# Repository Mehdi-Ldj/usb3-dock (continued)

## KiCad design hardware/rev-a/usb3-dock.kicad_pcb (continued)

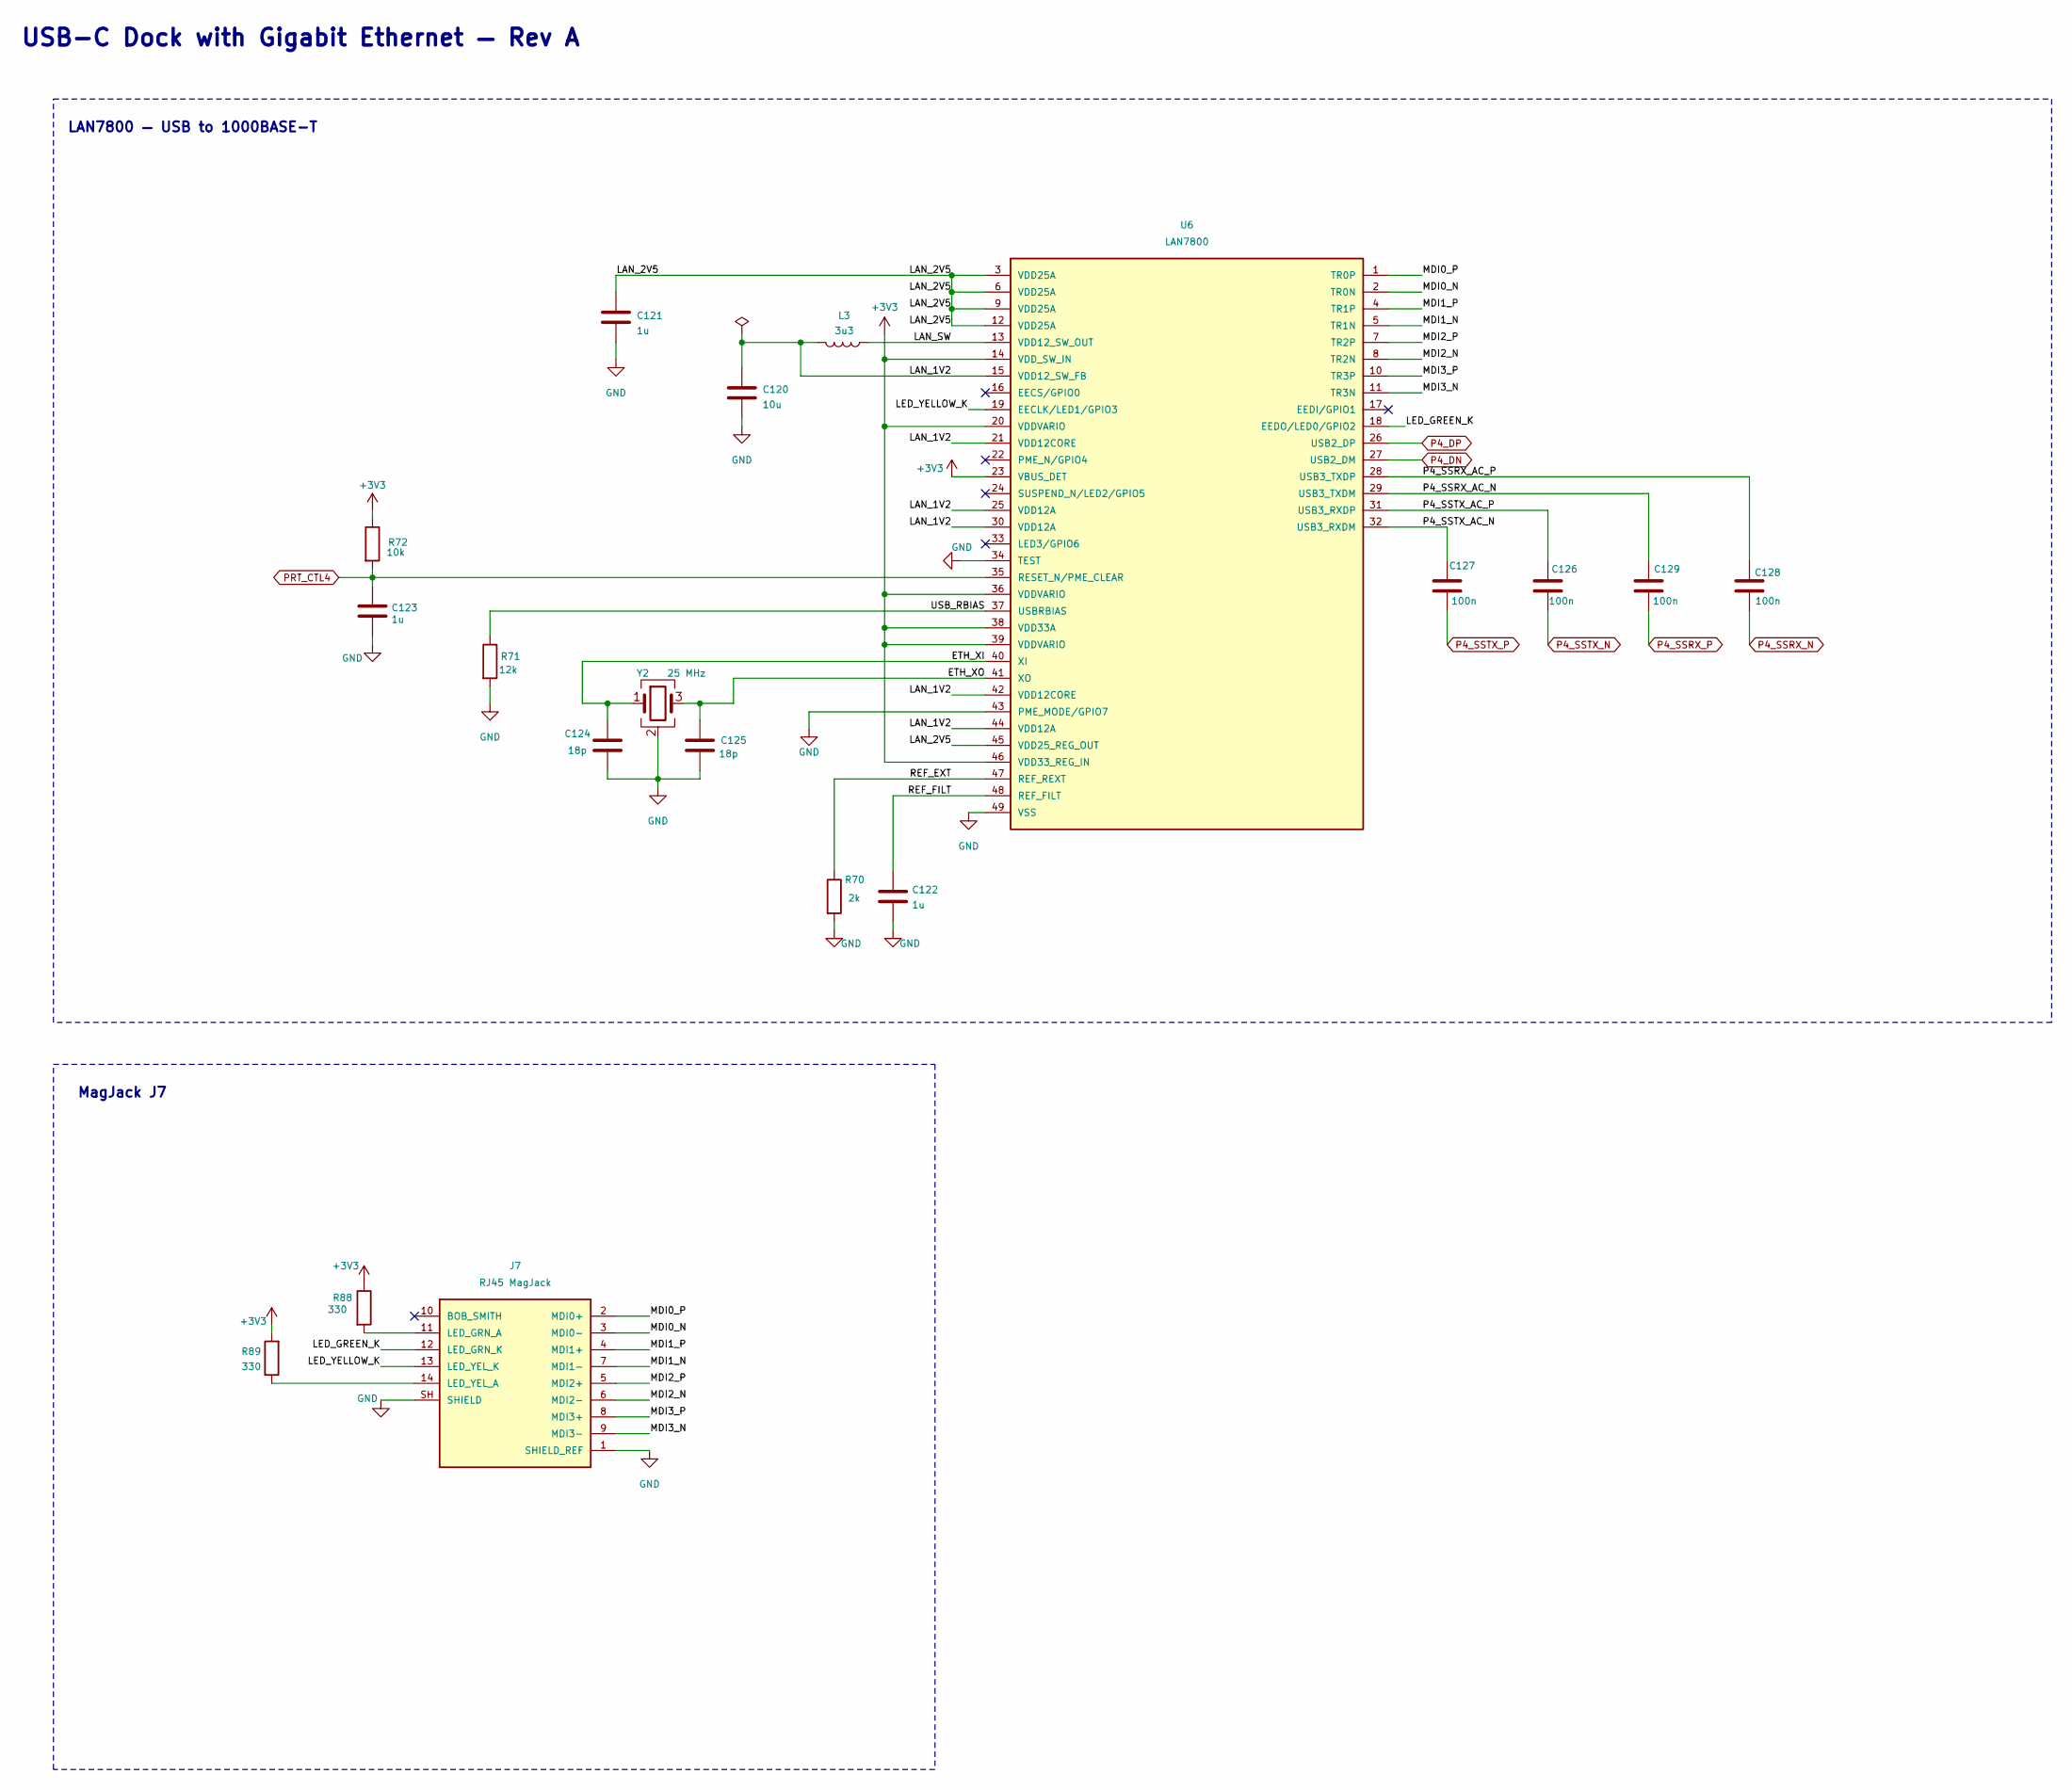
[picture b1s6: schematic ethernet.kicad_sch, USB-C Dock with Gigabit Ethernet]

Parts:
C120: 10u; C_0805_2012Metric
C121, C122, C123: 1u; C_0603_1608Metric
C124, C125: 18p; C_0402_1005Metric
C126, C127, C128, C129: 100n; C_0402_1005Metric
J7: RJ45 MagJack; RJ45_Hanrun_HR911130A
L3: 3u3; L_4x4mm_FNR4030
R70: 2k; R_0603_1608Metric
R71: 12k; R_0603_1608Metric
R72: 10k; R_0603_1608Metric
R88, R89: 330; R_0603_1608Metric
U6: LAN7800; QFN-48-1EP_6x6mm_P0.4mm_EP4.3x4.3mm
Y2: 25 MHz; Crystal_SMD_3225-4Pin_3.2x2.5mm

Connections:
+3V3: R72.1, R88.1, R89.2, U6.14 (VDD_SW_IN), U6.20 (VDDVARIO), U6.23 (VBUS_DET), U6.36 (VDDVARIO), U6.38 (VDD33A), U6.39 (VDDVARIO), U6.46 (VDD33_REG_IN); also elsewhere on the board
/ethernet/ETH_XI: C124.1, U6.40 (XI), Y2.1
/ethernet/ETH_XO: C125.1, U6.41 (XO), Y2.3
/ethernet/LAN_1V2: C120.1, L3.2, U6.15 (VDD12_SW_FB), U6.21 (VDD12CORE), U6.25 (VDD12A), U6.30 (VDD12A), U6.42 (VDD12CORE), U6.44 (VDD12A)
/ethernet/LAN_2V5: C121.1, U6.3 (VDD25A), U6.6 (VDD25A), U6.9 (VDD25A), U6.12 (VDD25A), U6.45 (VDD25_REG_OUT)
/ethernet/LAN_SW: L3.1, U6.13 (VDD12_SW_OUT)
/ethernet/LED_GREEN_K: J7.12 (LED_GRN_K), U6.18 (EEDO/LED0/GPIO2)
/ethernet/LED_YELLOW_K: J7.13 (LED_YEL_K), U6.19 (EECLK/LED1/GPIO3)
/ethernet/MDI0_N: J7.3 (MDI0-), U6.2 (TR0N)
/ethernet/MDI0_P: J7.2 (MDI0+), U6.1 (TR0P)
/ethernet/MDI1_N: J7.7 (MDI1-), U6.5 (TR1N)
/ethernet/MDI1_P: J7.4 (MDI1+), U6.4 (TR1P)
/ethernet/MDI2_N: J7.6 (MDI2-), U6.8 (TR2N)
/ethernet/MDI2_P: J7.5 (MDI2+), U6.7 (TR2P)
/ethernet/MDI3_N: J7.9 (MDI3-), U6.11 (TR3N)
/ethernet/MDI3_P: J7.8 (MDI3+), U6.10 (TR3P)
/ethernet/P4_SSRX_AC_N: C129.2, U6.29 (USB3_TXDM)
/ethernet/P4_SSRX_AC_P: C128.2, U6.28 (USB3_TXDP)
/ethernet/P4_SSTX_AC_N: C127.2, U6.32 (USB3_RXDM)
/ethernet/P4_SSTX_AC_P: C126.2, U6.31 (USB3_RXDP)
/ethernet/REF_EXT: R70.1, U6.47 (REF_REXT)
/ethernet/REF_FILT: C122.1, U6.48 (REF_FILT)
/ethernet/USB_RBIAS: R71.1, U6.37 (USBRBIAS)
GND: C120.2, C121.2, C122.2, C123.2, C124.2, C125.2, J7.1 (SHIELD_REF), J7.SH (SHIELD), R70.2, R71.2, U6.34 (TEST), U6.43 (PME_MODE/GPIO7), U6.49 (VSS), Y2.2 (G), Y2.4 (G); also elsewhere on the board
unnamed: J7.11 (LED_GRN_A), R88.2
unnamed: J7.14 (LED_YEL_A), R89.1
P4_DN: U6.27 (USB2_DM); also elsewhere on the board
P4_DP: U6.26 (USB2_DP); also elsewhere on the board
P4_SSRX_N: C128.1; also elsewhere on the board
P4_SSRX_P: C129.1; also elsewhere on the board
P4_SSTX_N: C126.1; also elsewhere on the board
P4_SSTX_P: C127.1; also elsewhere on the board
PRT_CTL4: C123.1, R72.2, U6.35 (RESET_N/PME_CLEAR); also elsewhere on the board

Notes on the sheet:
MagJack J7
USB-C Dock with Gigabit Ethernet — Rev A
LAN7800 — USB to 1000BASE-T

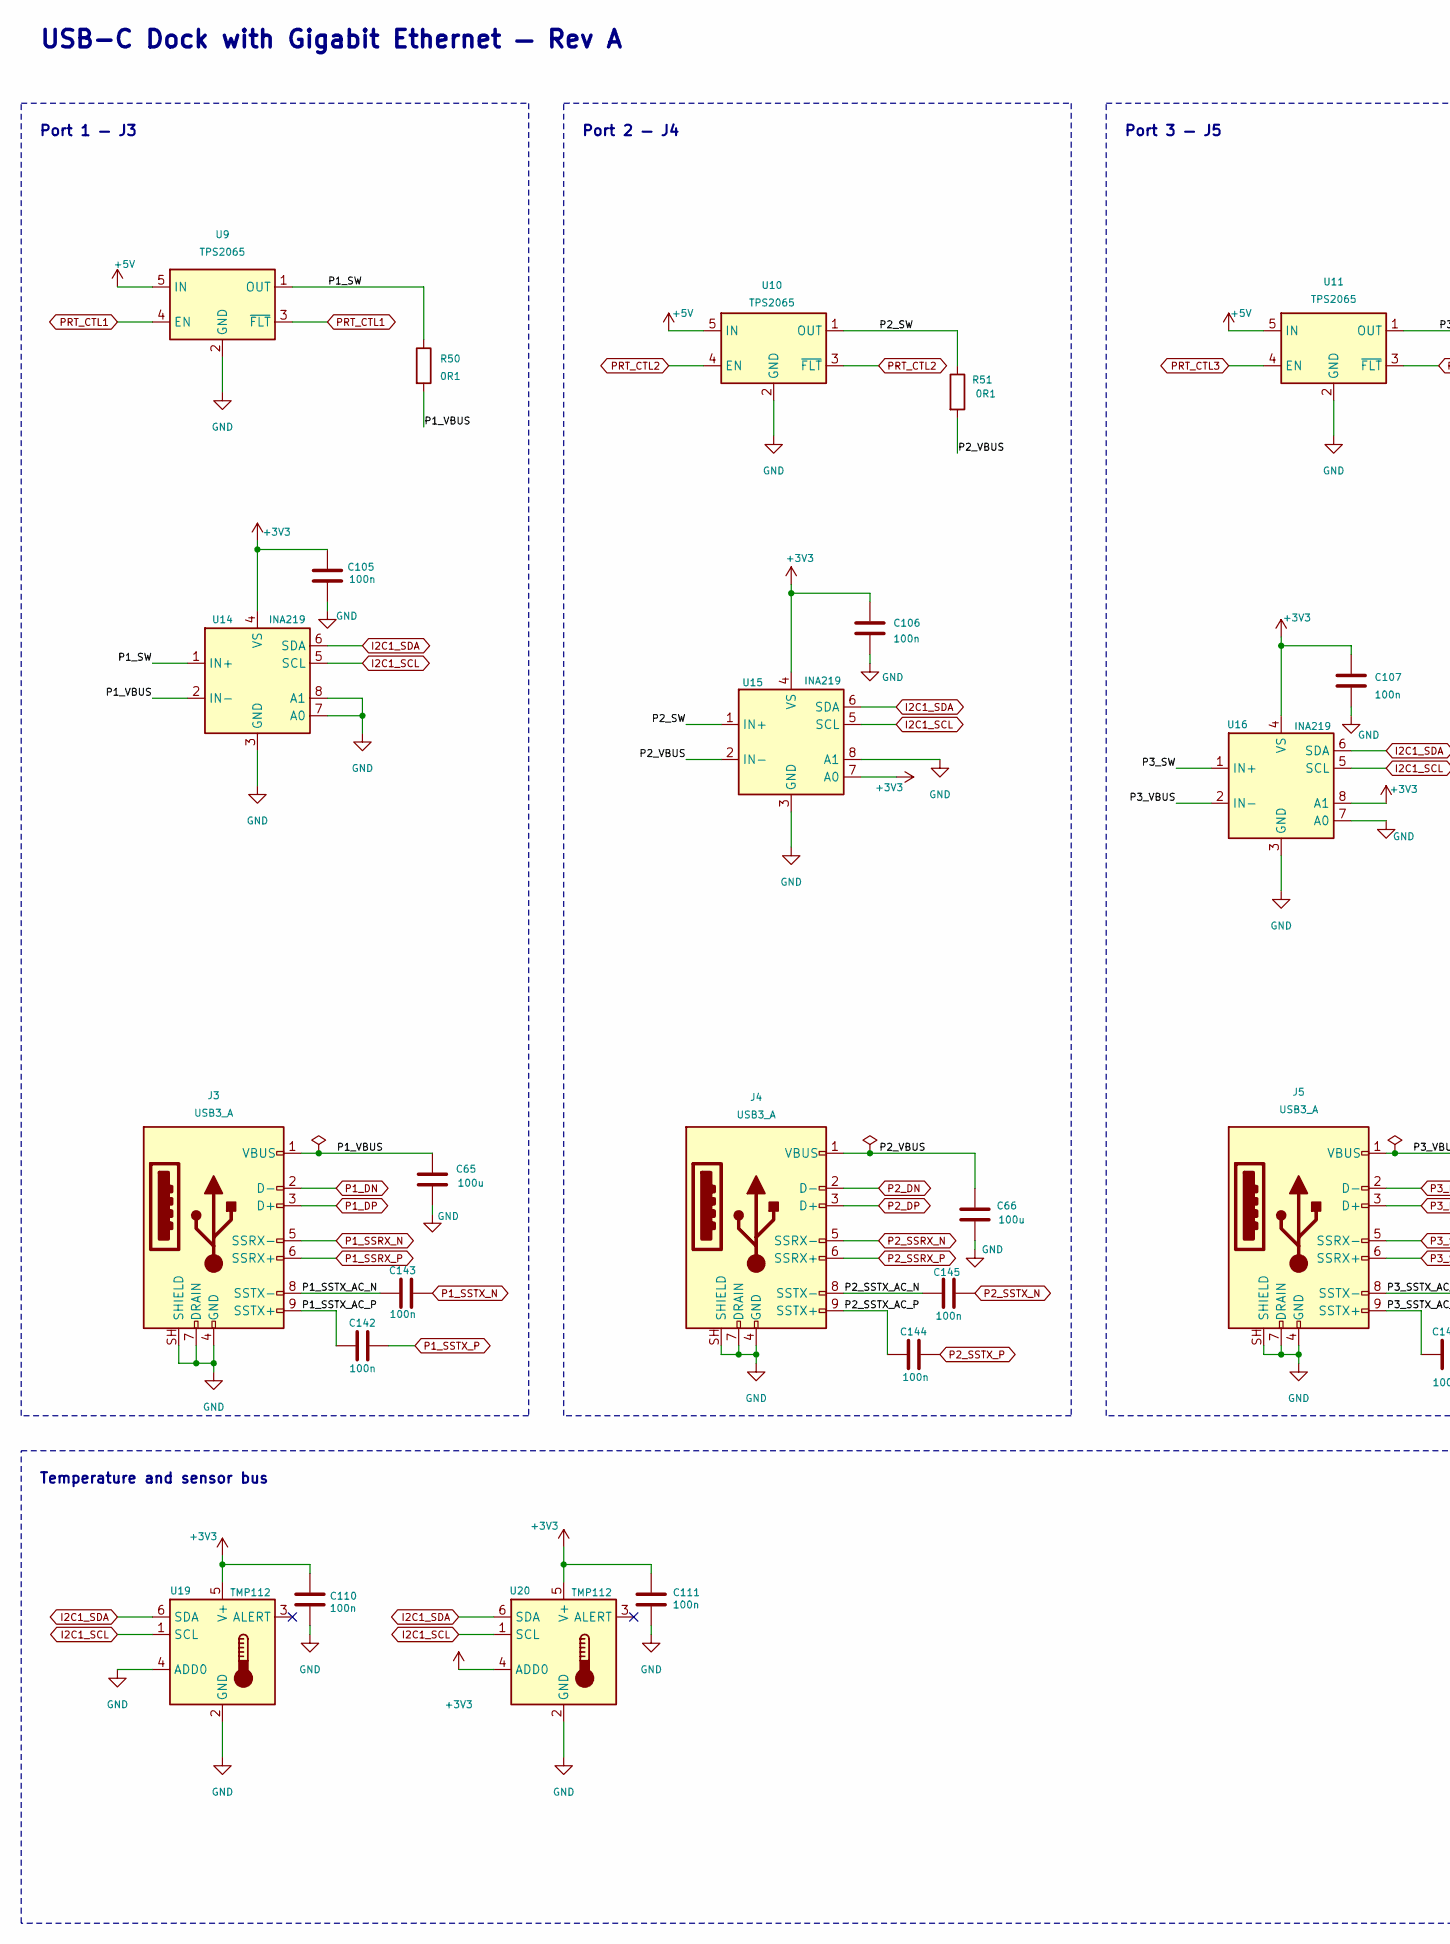
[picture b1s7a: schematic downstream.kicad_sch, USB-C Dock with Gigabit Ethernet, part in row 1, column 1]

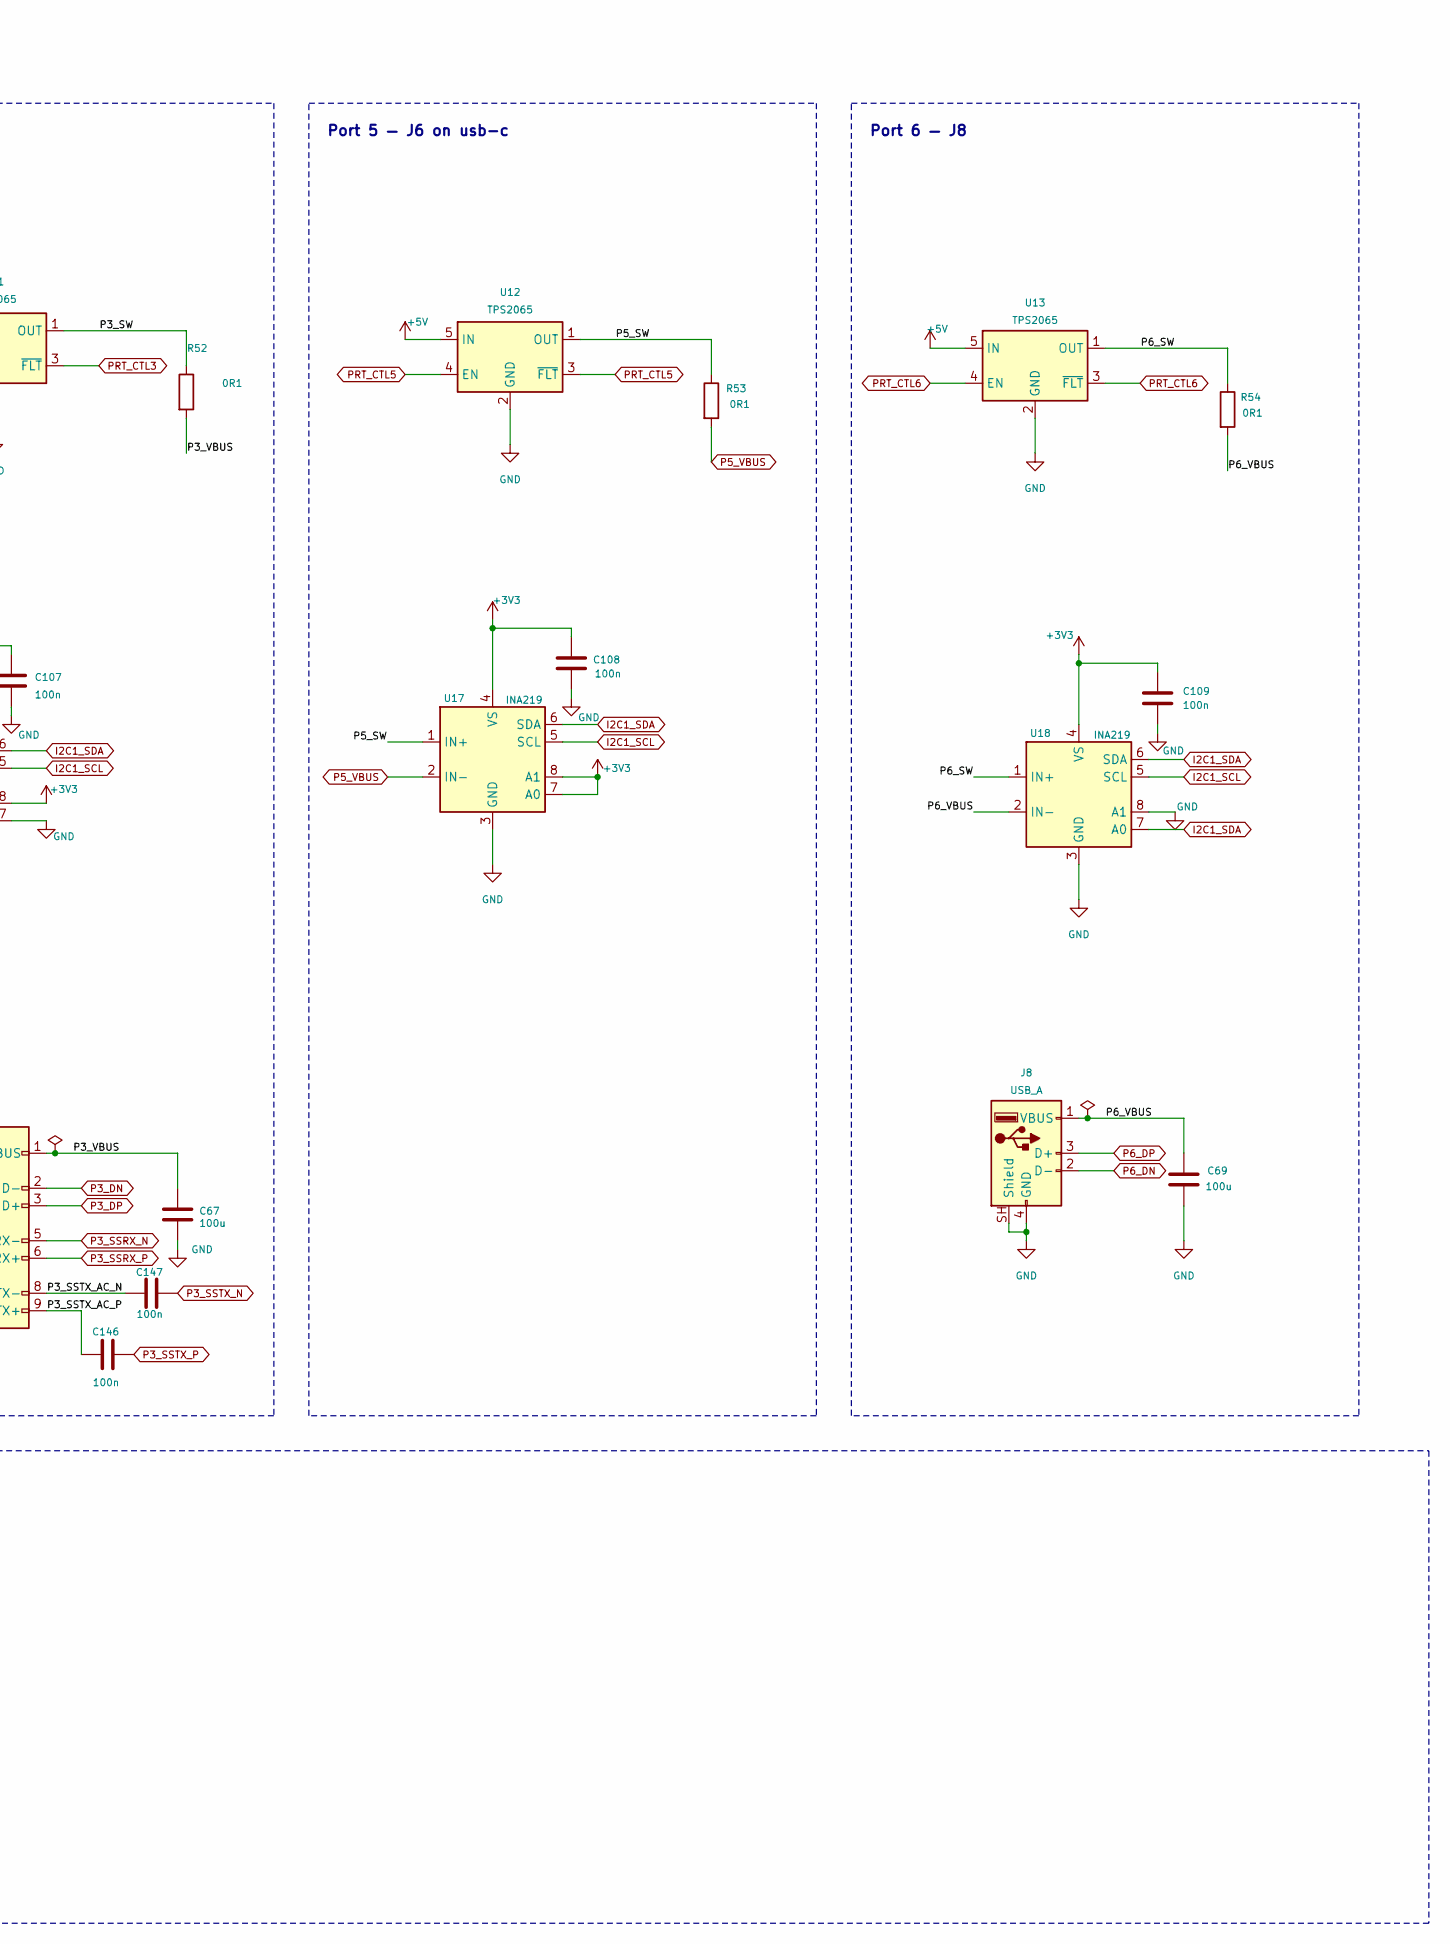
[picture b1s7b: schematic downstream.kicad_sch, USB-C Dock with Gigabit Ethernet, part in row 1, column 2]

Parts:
C65, C66, C67, C69: 100u; C_1210_3225Metric
C105, C106, C107, C108, C109, C110, C111, C142, C143, C144, C145, C146, C147: 100n; C_0402_1005Metric
J3, J4, J5: USB3_A; USB_A_Receptacle_XKB_U231-091N-4BLRA00-S
J8: USB_A; USB_A_Molex_67643_Horizontal
R50, R51, R52, R53, R54: 0R1; R_0805_2012Metric
U9, U10, U11, U12, U13: TPS2065; SOT-23-5
U14, U15, U16, U17, U18: INA219; SOT-23-8
U19, U20: TMP112; SOT-563

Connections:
+3V3: C105.1, C106.1, C107.1, C108.1, C109.1, C110.1, C111.1, U14.4 (VS), U15.4 (VS), U15.7 (A0), U16.4 (VS), U16.8 (A1), U17.4 (VS), U17.7 (A0), U17.8 (A1), U18.4 (VS), U19.5 (V+), U20.4 (ADD0), U20.5 (V+); also elsewhere on the board
+5V: U9.5 (IN), U10.5 (IN), U11.5 (IN), U12.5 (IN), U13.5 (IN); also elsewhere on the board
/downstream/P1_SSTX_AC_N: C143.1, J3.8 (SSTX-)
/downstream/P1_SSTX_AC_P: C142.1, J3.9 (SSTX+)
/downstream/P1_SW: R50.1, U9.1 (OUT), U14.1 (IN+)
/downstream/P1_VBUS: C65.1, J3.1 (VBUS), R50.2, U14.2 (IN-)
/downstream/P2_SSTX_AC_N: C145.1, J4.8 (SSTX-)
/downstream/P2_SSTX_AC_P: C144.1, J4.9 (SSTX+)
/downstream/P2_SW: R51.1, U10.1 (OUT), U15.1 (IN+)
/downstream/P2_VBUS: C66.1, J4.1 (VBUS), R51.2, U15.2 (IN-)
/downstream/P3_SSTX_AC_N: C147.1, J5.8 (SSTX-)
/downstream/P3_SSTX_AC_P: C146.1, J5.9 (SSTX+)
/downstream/P3_SW: R52.1, U11.1 (OUT), U16.1 (IN+)
/downstream/P3_VBUS: C67.1, J5.1 (VBUS), R52.2, U16.2 (IN-)
/downstream/P5_SW: R53.1, U12.1 (OUT), U17.1 (IN+)
/downstream/P6_SW: R54.1, U13.1 (OUT), U18.1 (IN+)
/downstream/P6_VBUS: C69.1, J8.1 (VBUS), R54.2, U18.2 (IN-)
GND: C65.2, C66.2, C67.2, C69.2, C105.2, C106.2, C107.2, C108.2, C109.2, C110.2, C111.2, J3.4 (GND), J3.7 (DRAIN), J3.SH (SHIELD), J4.4 (GND), J4.7 (DRAIN), J4.SH (SHIELD), J5.4 (GND), J5.7 (DRAIN), J5.SH (SHIELD), J8.4 (GND), J8.SH (Shield), U9.2 (GND), U10.2 (GND), U11.2 (GND), U12.2 (GND), U13.2 (GND), U14.3 (GND), U14.7 (A0), U14.8 (A1), U15.3 (GND), U15.8 (A1), U16.3 (GND), U16.7 (A0), U17.3 (GND), U18.3 (GND), U18.8 (A1), U19.2 (GND), U19.4 (ADD0), U20.2 (GND); also elsewhere on the board
I2C1_SCL: U14.5 (SCL), U15.5 (SCL), U16.5 (SCL), U17.5 (SCL), U18.5 (SCL), U19.1 (SCL), U20.1 (SCL); also elsewhere on the board
I2C1_SDA: U14.6 (SDA), U15.6 (SDA), U16.6 (SDA), U17.6 (SDA), U18.6 (SDA), U18.7 (A0), U19.6 (SDA), U20.6 (SDA); also elsewhere on the board
P1_DN: J3.2 (D-); also elsewhere on the board
P1_DP: J3.3 (D+); also elsewhere on the board
P1_SSRX_N: J3.5 (SSRX-); also elsewhere on the board
P1_SSRX_P: J3.6 (SSRX+); also elsewhere on the board
P1_SSTX_N: C143.2; also elsewhere on the board
P1_SSTX_P: C142.2; also elsewhere on the board
P2_DN: J4.2 (D-); also elsewhere on the board
P2_DP: J4.3 (D+); also elsewhere on the board
P2_SSRX_N: J4.5 (SSRX-); also elsewhere on the board
P2_SSRX_P: J4.6 (SSRX+); also elsewhere on the board
P2_SSTX_N: C145.2; also elsewhere on the board
P2_SSTX_P: C144.2; also elsewhere on the board
P3_DN: J5.2 (D-); also elsewhere on the board
P3_DP: J5.3 (D+); also elsewhere on the board
P3_SSRX_N: J5.5 (SSRX-); also elsewhere on the board
P3_SSRX_P: J5.6 (SSRX+); also elsewhere on the board
P3_SSTX_N: C147.2; also elsewhere on the board
P3_SSTX_P: C146.2; also elsewhere on the board
P5_VBUS: R53.2, U17.2 (IN-); also elsewhere on the board
P6_DN: J8.2 (D-); also elsewhere on the board
P6_DP: J8.3 (D+); also elsewhere on the board
PRT_CTL1: U9.3 (~FLT), U9.4 (EN); also elsewhere on the board
PRT_CTL2: U10.3 (~FLT), U10.4 (EN); also elsewhere on the board
PRT_CTL3: U11.3 (~FLT), U11.4 (EN); also elsewhere on the board
PRT_CTL5: U12.3 (~FLT), U12.4 (EN); also elsewhere on the board
PRT_CTL6: U13.3 (~FLT), U13.4 (EN); also elsewhere on the board

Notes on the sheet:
Port 2 — J4
Port 3 — J5
Port 6 — J8
Port 1 — J3
Temperature and sensor bus
USB-C Dock with Gigabit Ethernet — Rev A
Port 5 — J6 on usb-c

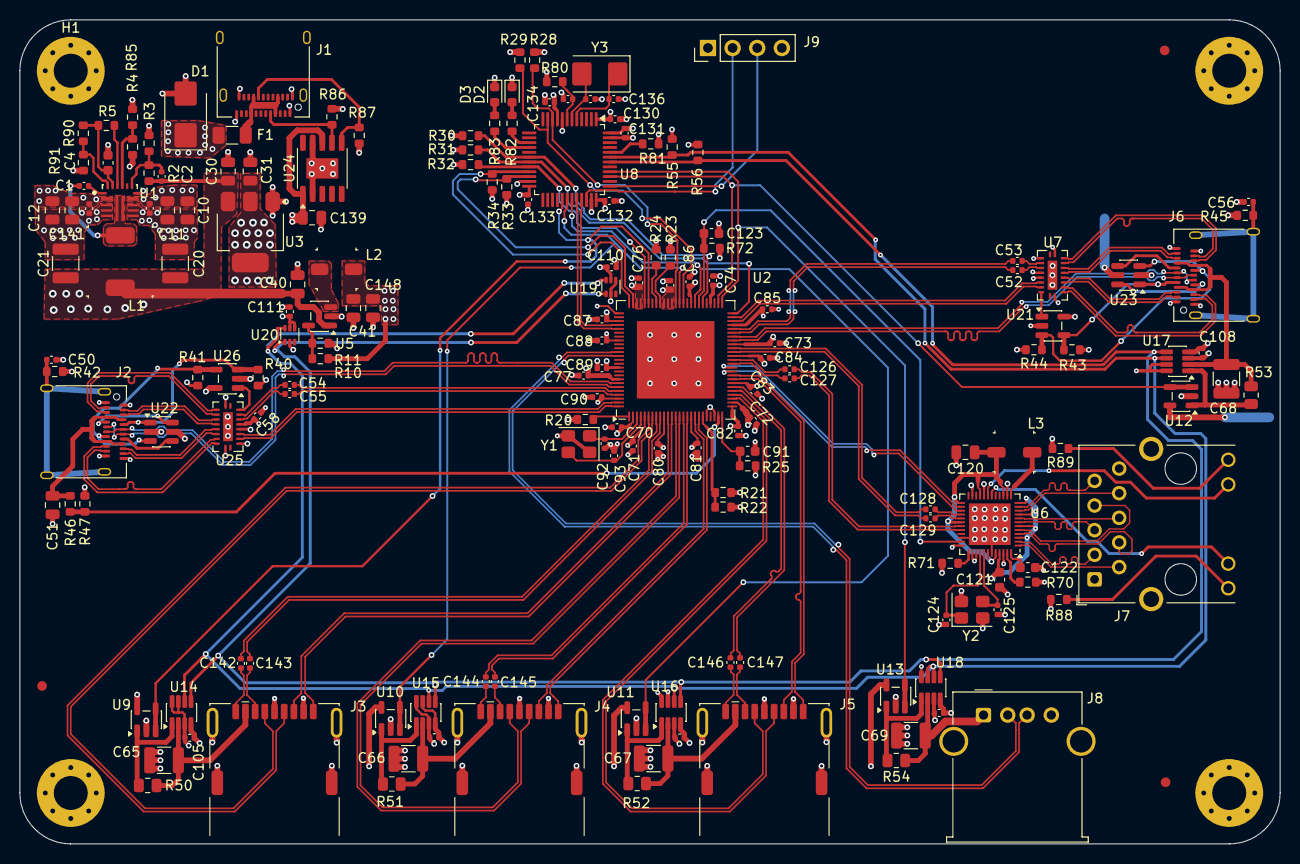
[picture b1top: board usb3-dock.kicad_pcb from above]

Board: 4 copper layers, 130.0 x 85.0 mm, 182 parts (0 on the bottom side), 163 nets.

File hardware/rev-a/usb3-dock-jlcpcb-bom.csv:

Comment,Designator,Footprint,JLCPCB Part #,MPN
100n,"C1,C50,C52,C53,C54,C55,C56,C58,C70,C71,C72,C73,C74,C75,C76,C77,C80,C81,C82,C83,C84,C85,C86,C87,C88,C89,C90,C105,C106,C107,C108,C109,C110,C111,C126,C127,C128,C129,C130,C131,C132,C133,C134,C138,C142,C143,C144,C145,C146,C147",Capacitor_SMD:C_0402_1005Metric,C1525,CL05B104KO5NNNC
100p,C2,Capacitor_SMD:C_0402_1005Metric,C1546,0402CG101J500NT
4u7,C4,Capacitor_SMD:C_0603_1608Metric,C326580,CC0603KRX5R8BB475
10u,"C10,C11,C12,C30,C31,C40,C41,C51,C120,C141,C148",Capacitor_SMD:C_0805_2012Metric,C380332,TCC0805X5R106K160FT
100n,"C13,C140",Capacitor_SMD:C_0402_1005Metric,C307331,CL05B104KB54PNC
100u,"C20,C21,C65,C66,C67,C68,C69",Capacitor_SMD:C_1210_3225Metric,C6120014,CGA1210X5R107M160RT
1u,"C91,C121,C122,C123",Capacitor_SMD:C_0603_1608Metric,C696901,TCC0603X5R105K160CT
18p,"C92,C93,C124,C125,C136,C137",Capacitor_SMD:C_0402_1005Metric,C1549,0402CG180J500NT
1u,C139,Capacitor_SMD:C_0805_2012Metric,C89190,0805B105K250NT
SMBJ15A,D1,Diode_SMD:D_SMB,C113988,SMBJ15A
LED,"D2,D3",LED_SMD:LED_0603_1608Metric,C2286,KT-0603R
3A,F1,Fuse:Fuse_1206_3216Metric,C41342,0468003.NRHF
USB_C,"J1,J2,J6",Connector_USB:USB_C_Receptacle_Amphenol_12401610E4-2A,C5119948,12401610E4#2A
USB3_A,"J3,J4,J5",dock:USB_A_Receptacle_XKB_U231-091N-4BLRA00-S,C2880618,U231-091N-4BLRA00-S
RJ45 MagJack,J7,dock:RJ45_Hanrun_HR911130A,C54408,HR911130A
USB_A,J8,Connector_USB:USB_A_Molex_67643_Horizontal,C564920,67643-2910
SWD,J9,Connector_PinHeader_2.54mm:PinHeader_1x04_P2.54mm_Vertical,C2691448,PZ254V-11-04P
4u7,L1,dock:L_7.1x6.6mm_CMLO0650H,C439009,CMLO0650H4R7MTT
2u2,L2,dock:L_4x4mm_PNR4020,C54620130,PNR4020-2R2M
3u3,L3,dock:L_4x4mm_FNR4030,C167870,FNR4030S3R3MT
73k2,R2,Resistor_SMD:R_0603_1608Metric,C14890,0603WAF7322T5E
56k,"R4,R43,R44",Resistor_SMD:R_0603_1608Metric,C23206,0603WAF5602T5E
100k,"R10,R11,R28,R29,R30,R31,R32,R46,R47",Resistor_SMD:R_0603_1608Metric,C25803,0603WAF1003T5E
12k,"R20,R71",Resistor_SMD:R_0603_1608Metric,C22790,0603WAF1202T5E
200k,"R21,R23,R24,R90",Resistor_SMD:R_0603_1608Metric,C25811,0603WAF2003T5E
10k,"R3,R5,R25,R33,R34,R72,R80,R81,R85,R91",Resistor_SMD:R_0603_1608Metric,C25804,0603WAF1002T5E
5k1,"R40,R41,R86,R87",Resistor_SMD:R_0603_1608Metric,C23186,0603WAF5101T5E
330,"R42,R45,R88,R89",Resistor_SMD:R_0603_1608Metric,C23138,0603WAF3300T5E
0R1,"R50,R51,R52,R53,R54",Resistor_SMD:R_0805_2012Metric,C160917,RL10FTNR100
4k7,"R55,R56",Resistor_SMD:R_0603_1608Metric,C23162,0603WAF4701T5E
2k,R70,Resistor_SMD:R_0603_1608Metric,C22975,0603WAF2001T5E
1k,"R82,R83",Resistor_SMD:R_0603_1608Metric,C21190,0603WAF1001T5E
TPS56C215,U1,dock:Texas_RNN0018A_TPS56C215,C473372,TPS56C215RNNR
USB5807C,U2,dock:VQFN-100-1EP_12x12mm_P0.4mm_EP8x8mm,C628616,USB5807CT/KD
TLV76133,U3,Package_TO_SOT_SMD:SOT-223-3_TabPin2,C7527500,TLV76133DCYR
TLV62569,U5,Package_TO_SOT_SMD:SOT-23-5,C141836,TLV62569DBVR
LAN7800,U6,dock:QFN-48-1EP_6x6mm_P0.4mm_EP4.3x4.3mm,C625080,LAN7800T-I/VSX
STM32F072C8,U8,Package_QFP:LQFP-48_7x7mm_P0.5mm,C80488,STM32F072C8T6
TPS2065,"U9,U10,U11,U12,U13",Package_TO_SOT_SMD:SOT-23-5,C133792,TPS2065DBVR
INA219,"U14,U15,U16,U17,U18",Package_TO_SOT_SMD:SOT-23-8,C87469,INA219AIDCNR
TMP112,"U19,U20",Package_TO_SOT_SMD:SOT-563,C3019123,TMP112BIDRLR
TLV7031,"U21,U26",Package_TO_SOT_SMD:SOT-23-5,C2869832,TLV7031DBVR
SRV05-4,"U22,U23",Package_TO_SOT_SMD:SOT-23-6,C13612,SRV05-4.TCT
CH224A,U24,Package_SO:SSOP-10-1EP_3.9x4.9mm_P1mm_EP2.1x3.3mm,C42459160,CH224A
HD3SS3212,"U7,U25",dock:DHVQFN-20-1EP_2.5x4.5mm_P0.5mm_EP1x3mm_TI,C544517,HD3SS3212IRKSR
25 MHz,"Y1,Y2",Crystal:Crystal_SMD_3225-4Pin_3.2x2.5mm,C70582,X322525MMB4SI
8 MHz,Y3,Crystal:Crystal_SMD_5032-2Pin_5.0x3.2mm,C115962,X50328MSB2GI
